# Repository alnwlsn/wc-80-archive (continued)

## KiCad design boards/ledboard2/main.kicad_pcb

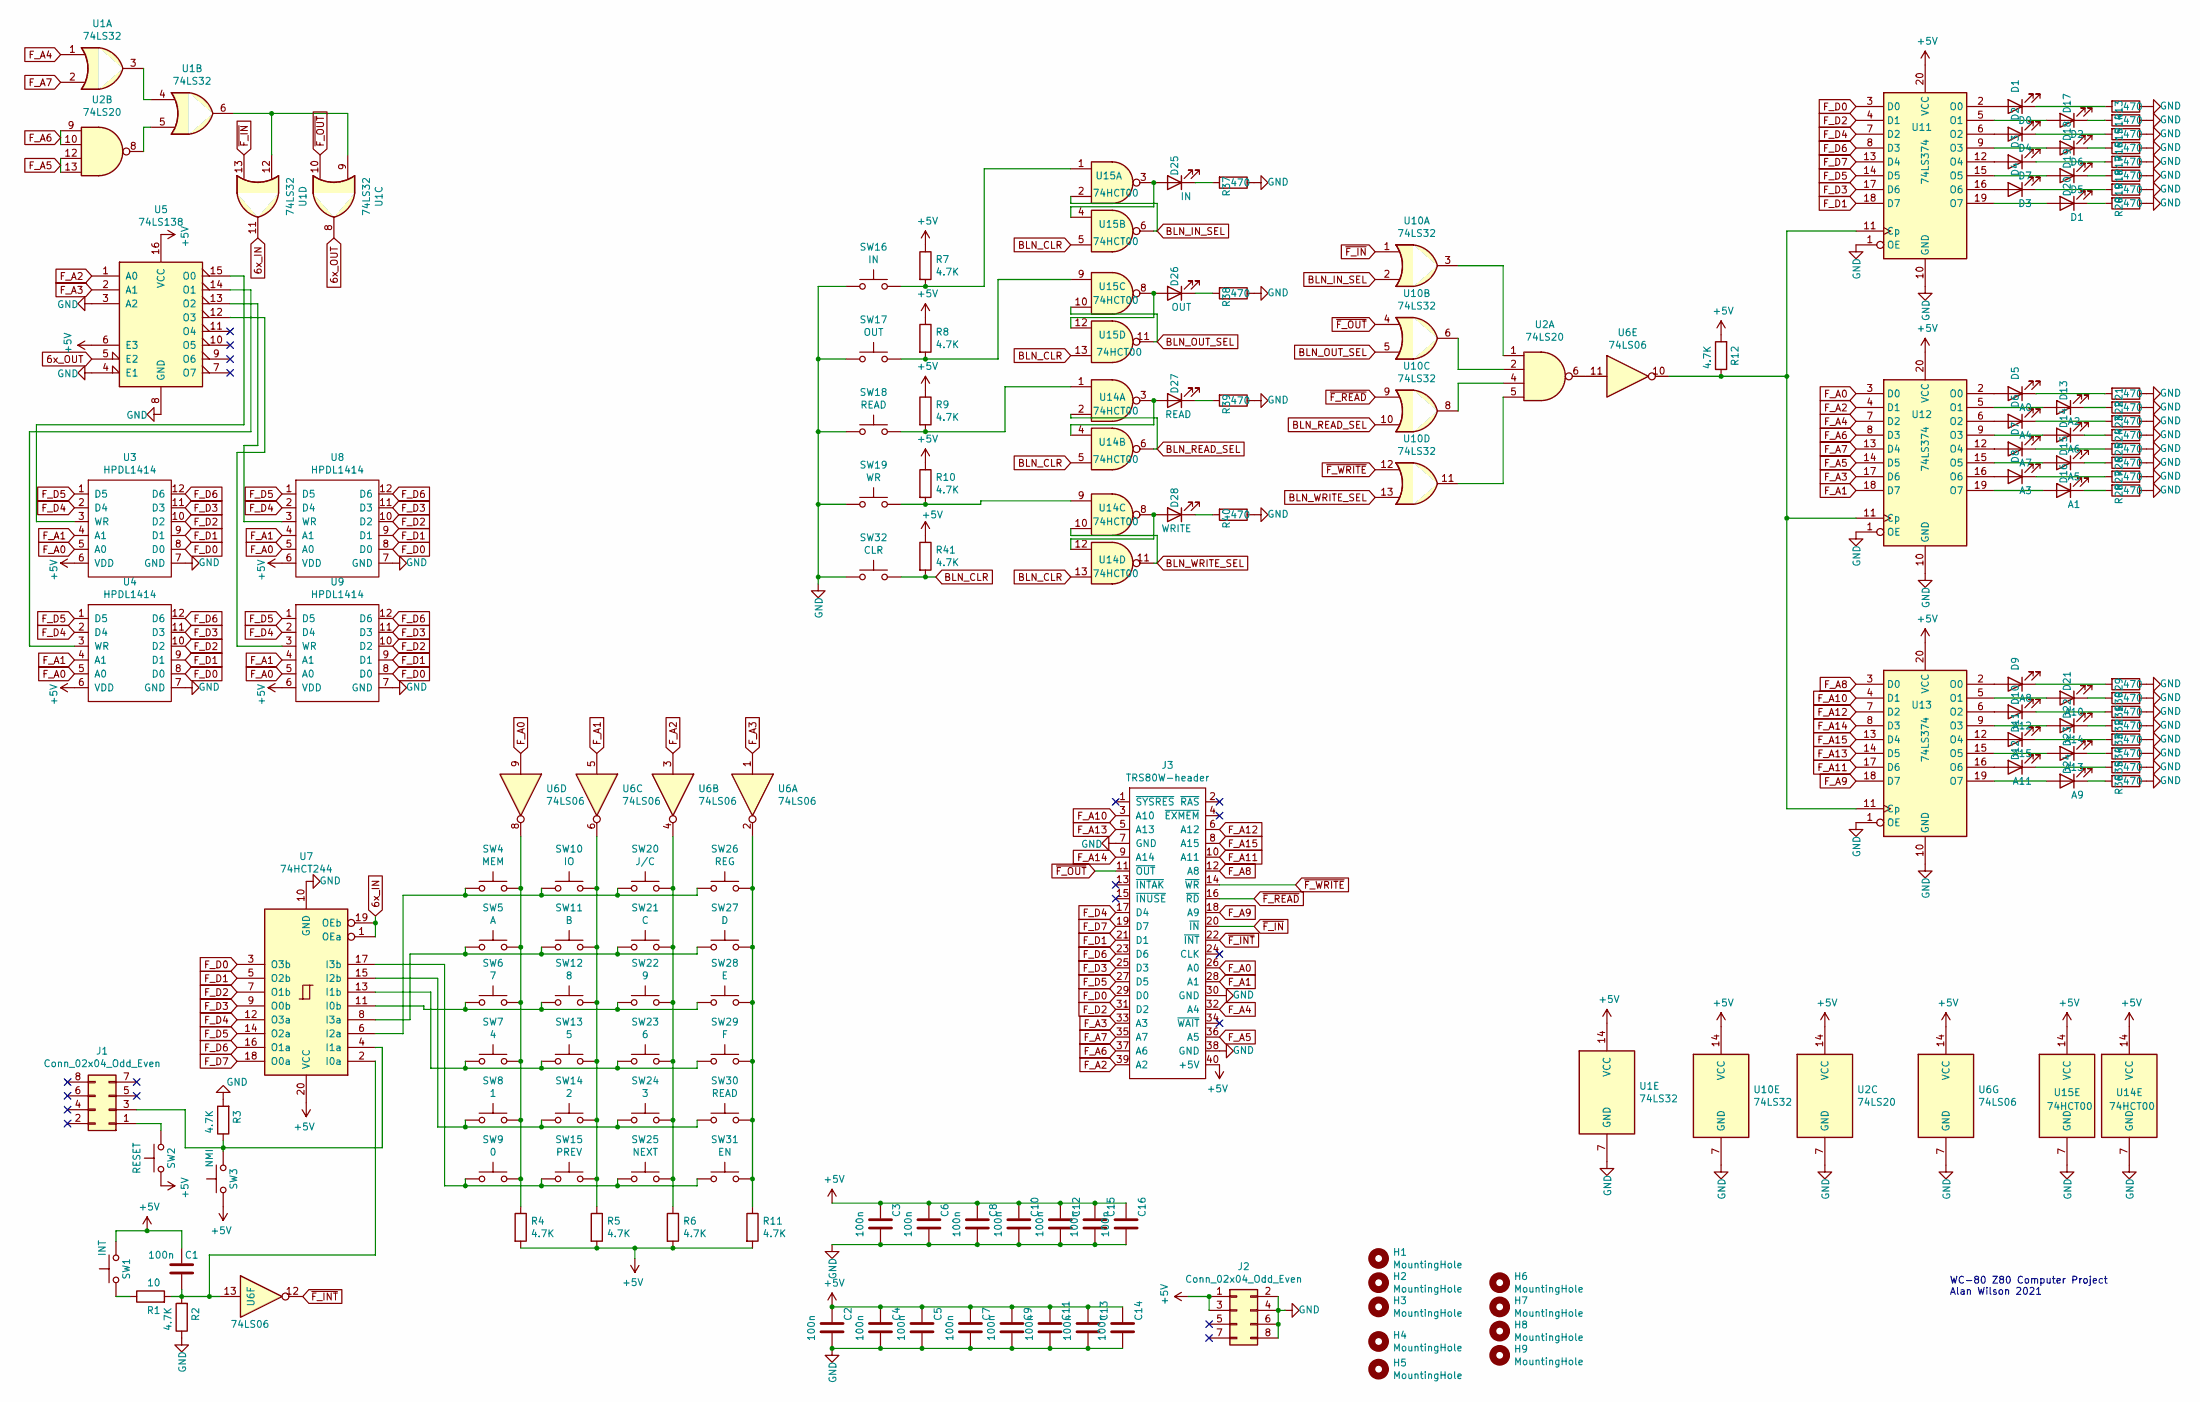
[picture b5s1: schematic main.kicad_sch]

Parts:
C1, C2, C3, C4, C5, C6, C7, C8, C9, C10, C11, C12, C13, C14, C15, C16: 100n; C_0805_2012Metric
D1: D0; LED_D3.0mm_FlatTop
D2: D4; LED_D3.0mm_FlatTop
D3: D7; LED_D3.0mm_FlatTop
D4: D3; LED_D3.0mm_FlatTop
D5: A0; LED_D3.0mm_FlatTop
D6: A4; LED_D3.0mm_FlatTop
D7: A7; LED_D3.0mm_FlatTop
D8: A3; LED_D3.0mm_FlatTop
D9: A8; LED_D3.0mm_FlatTop
D10: A12; LED_D3.0mm_FlatTop
D11: A15; LED_D3.0mm_FlatTop
D12: A11; LED_D3.0mm_FlatTop
D13: A2; LED_D3.0mm_FlatTop
D14: A6; LED_D3.0mm_FlatTop
D15: A5; LED_D3.0mm_FlatTop
D16: A1; LED_D3.0mm_FlatTop
D17: D2; LED_D3.0mm_FlatTop
D18: D6; LED_D3.0mm_FlatTop
D19: D5; LED_D3.0mm_FlatTop
D20: D1; LED_D3.0mm_FlatTop
D21: A10; LED_D3.0mm_FlatTop
D22: A14; LED_D3.0mm_FlatTop
D23: A13; LED_D3.0mm_FlatTop
D24: A9; LED_D3.0mm_FlatTop
D25: IN; LED_D3.0mm_FlatTop
D26: OUT; LED_D3.0mm_FlatTop
D27: READ; LED_D3.0mm_FlatTop
D28: WRITE; LED_D3.0mm_FlatTop
H1, H2, H3, H4, H5, H6, H7, H8, H9: MountingHole; MountingHole_3.2mm_M3_DIN965
J1, J2: Conn_02x04_Odd_Even; PinHeader_2x04_P2.54mm_Vertical
J3: TRS80W-header; PinHeader_2x20_P2.54mm_Vertical
R1: 10; R_0805_2012Metric
R2, R3, R4, R5, R6, R7, R8, R9, R10, R11, R12, R41: 4.7K; R_0805_2012Metric
R13, R14, R15, R16, R17, R18, R19, R20, R21, R22, R23, R24, R25, R26, R27, R28, R29, R30, R31, R32, R33, R34, R35, R36, R37, R38, R39, R40: 470; R_0805_2012Metric
SW1: INT; DTSL-6
SW2: RESET; DTSL-6
SW3: NMI; DTSL-6
SW4: MEM; DTSL-6
SW5: A; DTSL-6
SW6: 7; DTSL-6
SW7: 4; DTSL-6
SW8: 1; DTSL-6
SW9: 0; DTSL-6
SW10: IO; DTSL-6
SW11: B; DTSL-6
SW12: 8; DTSL-6
SW13: 5; DTSL-6
SW14: 2; DTSL-6
SW15: PREV; DTSL-6
SW16: IN; DTSL-6
SW17: OUT; DTSL-6
SW18, SW30: READ; DTSL-6
SW19: WR; DTSL-6
SW20: J/C; DTSL-6
SW21: C; DTSL-6
SW22: 9; DTSL-6
SW23: 6; DTSL-6
SW24: 3; DTSL-6
SW25: NEXT; DTSL-6
SW26: REG; DTSL-6
SW27: D; DTSL-6
SW28: E; DTSL-6
SW29: F; DTSL-6
SW31: EN; DTSL-6
SW32: CLR; DTSL-6
U1, U10: 74LS32; SOIC-14_3.9x8.7mm_P1.27mm
U2: 74LS20; SOIC-14_3.9x8.7mm_P1.27mm
U3, U4, U8, U9: HPDL1414; DIP-24_W15.24mm_Socket
U5: 74LS138; SOIC-16_3.9x9.9mm_P1.27mm
U6: 74LS06; SOIC-14_3.9x8.7mm_P1.27mm
U7: 74HCT244; SOIC-20W_7.5x12.8mm_P1.27mm
U11, U12, U13: 74LS374; SOIC-20W_7.5x12.8mm_P1.27mm
U14, U15: 74HCT00; SOIC-14_3.9x8.7mm_P1.27mm

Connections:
6x_IN: U1.11, U7.1 (OEa), U7.19 (OEb)
6x_OUT: U1.8, U5.5 (E2)
+5V: C1.2, C2.1, C3.1, C4.1, C5.1, C6.1, C7.1, C8.1, C9.1, C10.1, C11.1, C12.1, C13.1, C14.1, C15.1, C16.1, J2.1, J2.3, J3.40 (+5V), R4.2, R5.2, R6.2, R7.1, R8.1, R9.1, R10.1, R11.2, R12.2, R41.1, SW1.2, SW2.1, SW3.1, U1.14 (VCC), U2.14 (VCC), U3.6 (VDD), U4.6 (VDD), U5.6 (E3), U5.16 (VCC), U6.14 (VCC), U7.20 (VCC), U8.6 (VDD), U9.6 (VDD), U10.14 (VCC), U11.20 (VCC), U12.20 (VCC), U13.20 (VCC), U14.14 (VCC), U15.14 (VCC)
BLN_CLR: R41.2, SW32.2, U14.5, U14.13, U15.5, U15.13
BLN_IN_SEL: U10.2, U15.2, U15.6
BLN_OUT_SEL: U10.5, U15.10, U15.11
BLN_READ_SEL: U10.10, U14.2, U14.6
BLN_WRITE_SEL: U10.13, U14.10, U14.11
F_A0: J3.26 (A0), U3.5 (A0), U4.5 (A0), U6.9, U8.5 (A0), U9.5 (A0), U12.3 (D0)
F_A1: J3.28 (A1), U3.4 (A1), U4.4 (A1), U6.5, U8.4 (A1), U9.4 (A1), U12.18 (D7)
F_A2: J3.39 (A2), U5.1 (A0), U6.3, U12.4 (D1)
F_A3: J3.33 (A3), U5.2 (A1), U6.1, U12.17 (D6)
F_A4: J3.32 (A4), U1.1, U12.7 (D2)
F_A5: J3.36 (A5), U2.12, U2.13, U12.14 (D5)
F_A6: J3.37 (A6), U2.9, U2.10, U12.8 (D3)
F_A7: J3.35 (A7), U1.2, U12.13 (D4)
F_A8: J3.12 (A8), U13.3 (D0)
F_A9: J3.18 (A9), U13.18 (D7)
F_A10: J3.3 (A10), U13.4 (D1)
F_A11: J3.10 (A11), U13.17 (D6)
F_A12: J3.6 (A12), U13.7 (D2)
F_A13: J3.5 (A13), U13.14 (D5)
F_A14: J3.9 (A14), U13.8 (D3)
F_A15: J3.8 (A15), U13.13 (D4)
F_D0: J3.29 (D0), U3.8 (D0), U4.8 (D0), U7.3 (O3b), U8.8 (D0), U9.8 (D0), U11.3 (D0)
F_D1: J3.21 (D1), U3.9 (D1), U4.9 (D1), U7.5 (O2b), U8.9 (D1), U9.9 (D1), U11.18 (D7)
F_D2: J3.31 (D2), U3.10 (D2), U4.10 (D2), U7.7 (O1b), U8.10 (D2), U9.10 (D2), U11.4 (D1)
F_D3: J3.25 (D3), U3.11 (D3), U4.11 (D3), U7.9 (O0b), U8.11 (D3), U9.11 (D3), U11.17 (D6)
F_D4: J3.17 (D4), U3.2 (D4), U4.2 (D4), U7.12 (O3a), U8.2 (D4), U9.2 (D4), U11.7 (D2)
F_D5: J3.27 (D5), U3.1 (D5), U4.1 (D5), U7.14 (O2a), U8.1 (D5), U9.1 (D5), U11.14 (D5)
F_D6: J3.23 (D6), U3.12 (D6), U4.12 (D6), U7.16 (O1a), U8.12 (D6), U9.12 (D6), U11.8 (D3)
F_D7: J3.19 (D7), U7.18 (O0a), U11.13 (D4)
GND: C2.2, C3.2, C4.2, C5.2, C6.2, C7.2, C8.2, C9.2, C10.2, C11.2, C12.2, C13.2, C14.2, C15.2, C16.2, J2.2, J2.4, J2.6, J2.8, J3.7 (GND), J3.30 (GND), J3.38 (GND), R2.1, R3.2, R13.1, R14.1, R15.1, R16.1, R17.1, R18.1, R19.1, R20.1, R21.1, R22.1, R23.1, R24.1, R25.1, R26.1, R27.1, R28.1, R29.1, R30.1, R31.1, R32.1, R33.1, R34.1, R35.1, R36.1, R37.1, R38.1, R39.1, R40.1, SW16.1, SW17.1, SW18.1, SW19.1, SW32.1, U1.7 (GND), U2.7 (GND), U3.7 (GND), U4.7 (GND), U5.3 (A2), U5.4 (E1), U5.8 (GND), U6.7 (GND), U7.10 (GND), U8.7 (GND), U9.7 (GND), U10.7 (GND), U11.1 (OE), U11.10 (GND), U12.1 (OE), U12.10 (GND), U13.1 (OE), U13.10 (GND), U14.7 (GND), U15.7 (GND)
unnamed: D1.2 (A), U11.2 (O0)
unnamed: D1.1 (K), R13.2
unnamed: D2.2 (A), U11.6 (O2)
unnamed: D2.1 (K), R15.2
unnamed: D3.2 (A), U11.12 (O4)
unnamed: D3.1 (K), R17.2
unnamed: D4.2 (A), U11.16 (O6)
unnamed: D4.1 (K), R19.2
unnamed: D5.2 (A), U12.2 (O0)
unnamed: D5.1 (K), R21.2
unnamed: D6.2 (A), U12.6 (O2)
unnamed: D6.1 (K), R23.2
unnamed: D7.2 (A), U12.12 (O4)
unnamed: D7.1 (K), R25.2
unnamed: D8.2 (A), U12.16 (O6)
unnamed: D8.1 (K), R27.2
unnamed: D9.2 (A), U13.2 (O0)
unnamed: D9.1 (K), R29.2
unnamed: D10.2 (A), U13.6 (O2)
unnamed: D10.1 (K), R31.2
unnamed: D11.2 (A), U13.12 (O4)
unnamed: D11.1 (K), R33.2
unnamed: D12.2 (A), U13.16 (O6)
unnamed: D12.1 (K), R35.2
unnamed: D13.2 (A), U12.5 (O1)
unnamed: D13.1 (K), R22.2
unnamed: D14.2 (A), U12.9 (O3)
unnamed: D14.1 (K), R24.2
unnamed: D15.2 (A), U12.15 (O5)
unnamed: D15.1 (K), R26.2
unnamed: D16.2 (A), U12.19 (O7)
unnamed: D16.1 (K), R28.2
unnamed: D17.2 (A), U11.5 (O1)
unnamed: D17.1 (K), R14.2
unnamed: D18.2 (A), U11.9 (O3)
unnamed: D18.1 (K), R16.2
unnamed: D19.2 (A), U11.15 (O5)
unnamed: D19.1 (K), R18.2
unnamed: D20.2 (A), U11.19 (O7)
unnamed: D20.1 (K), R20.2
unnamed: D21.2 (A), U13.5 (O1)
unnamed: D21.1 (K), R30.2
unnamed: D22.2 (A), U13.9 (O3)
unnamed: D22.1 (K), R32.2
unnamed: D23.2 (A), U13.15 (O5)
unnamed: D23.1 (K), R34.2
unnamed: D24.2 (A), U13.19 (O7)
unnamed: D24.1 (K), R36.2
unnamed: D25.2 (A), U15.3, U15.4
unnamed: D25.1 (K), R37.2
unnamed: D26.2 (A), U15.8, U15.12
unnamed: D26.1 (K), R38.2
unnamed: D27.2 (A), U14.3, U14.4
unnamed: D27.1 (K), R39.2
unnamed: D28.2 (A), U14.8, U14.12
unnamed: D28.1 (K), R40.2
unnamed: J1.1, SW2.2
unnamed: J1.3, R3.1, SW3.2, U7.4 (I1a)
unnamed: R1.1, SW1.1
unnamed: R4.1, SW4.2, SW5.2, SW6.2, SW7.2, SW8.2, SW9.2, U6.8
unnamed: R5.1, SW10.2, SW11.2, SW12.2, SW13.2, SW14.2, SW15.2, U6.6
unnamed: R6.1, SW20.2, SW21.2, SW22.2, SW23.2, SW24.2, SW25.2, U6.4
unnamed: R7.2, SW16.2, U15.1
unnamed: R8.2, SW17.2, U15.9
unnamed: R9.2, SW18.2, U14.1
unnamed: R10.2, SW19.2, U14.9
unnamed: R11.1, SW26.2, SW27.2, SW28.2, SW29.2, SW30.2, SW31.2, U6.2
unnamed: U1.3, U1.4
unnamed: U1.5, U2.8
unnamed: U1.6, U1.9, U1.12
unnamed: U2.6, U6.11
unnamed: U3.3 (WR), U5.15 (O0)
unnamed: U4.3 (WR), U5.14 (O1)
unnamed: U5.13 (O2), U8.3 (WR)
unnamed: U5.12 (O3), U9.3 (WR)
unnamed: C1.1, R1.2, R2.2, U6.13, U7.2 (I0a)
unnamed: SW6.1, SW12.1, SW22.1, SW28.1, U7.11 (I0b)
unnamed: SW7.1, SW13.1, SW23.1, SW29.1, U7.13 (I1b)
unnamed: SW4.1, SW10.1, SW20.1, SW26.1, U7.6 (I2a)
unnamed: SW8.1, SW14.1, SW24.1, SW30.1, U7.15 (I2b)
unnamed: SW5.1, SW11.1, SW21.1, SW27.1, U7.8 (I3a)
unnamed: SW9.1, SW15.1, SW25.1, SW31.1, U7.17 (I3b)
unnamed: U2.1, U10.3
unnamed: U2.2, U10.6
unnamed: U2.4, U10.8
unnamed: U2.5, U10.11
unnamed: R12.1, U6.10, U11.11 (Cp), U12.11 (Cp), U13.11 (Cp)
~F_INT: J3.22 (~INT), U6.12
~F_IN: J3.20 (~IN), U1.13, U10.1
~F_OUT: J3.11 (~OUT), U1.10, U10.4
~F_READ: J3.16 (~RD), U10.9
~F_WRITE: J3.14 (~WR), U10.12

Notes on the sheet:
WC-80 Z80 Computer Project Alan Wilson 2021

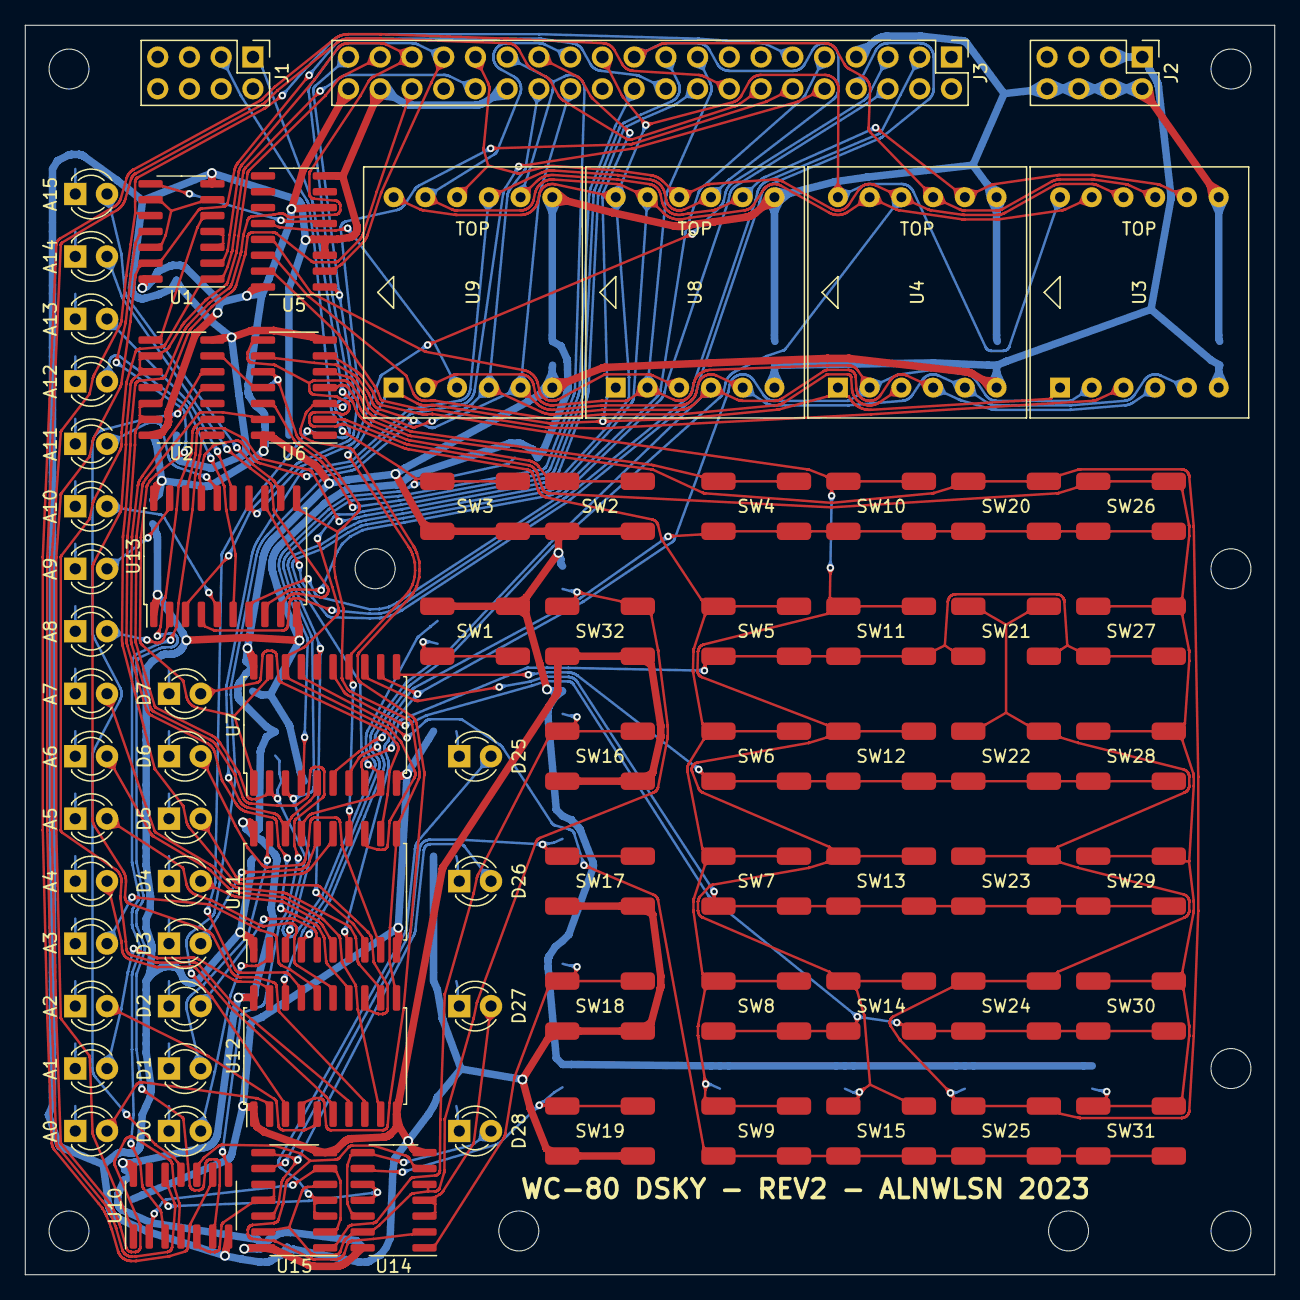
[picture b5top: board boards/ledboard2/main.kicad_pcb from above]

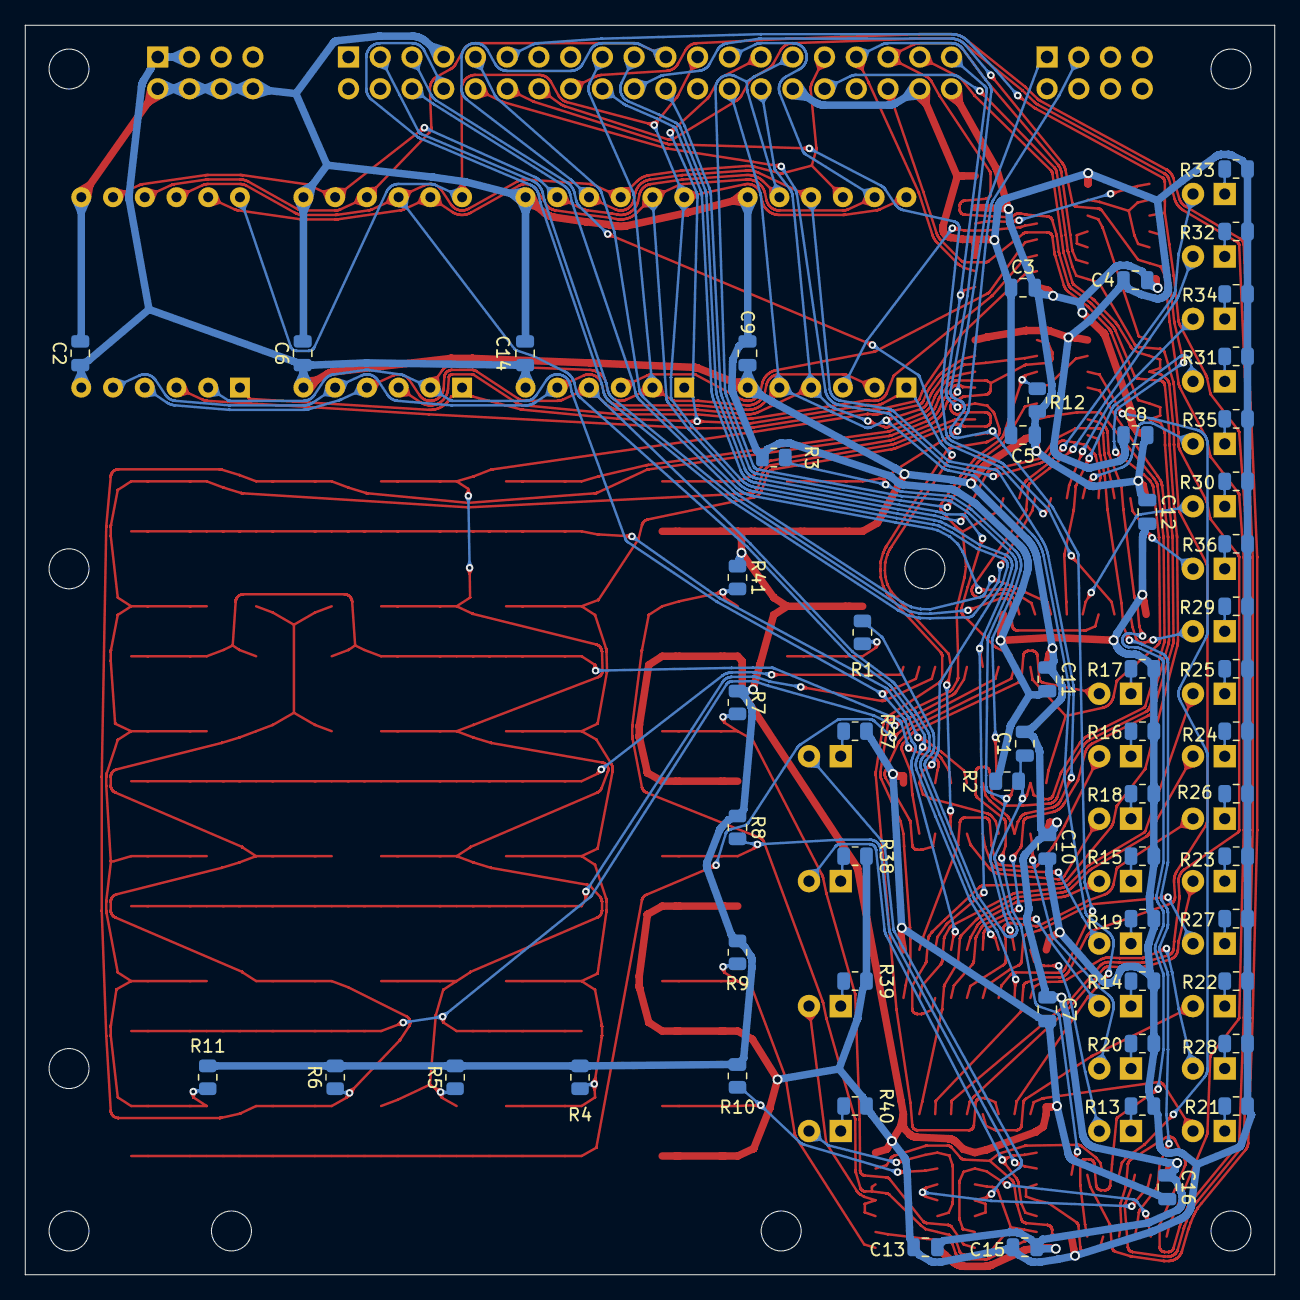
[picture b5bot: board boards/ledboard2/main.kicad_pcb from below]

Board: 2 copper layers, 100.0 x 100.0 mm, 144 parts (57 on the bottom side), 125 nets.

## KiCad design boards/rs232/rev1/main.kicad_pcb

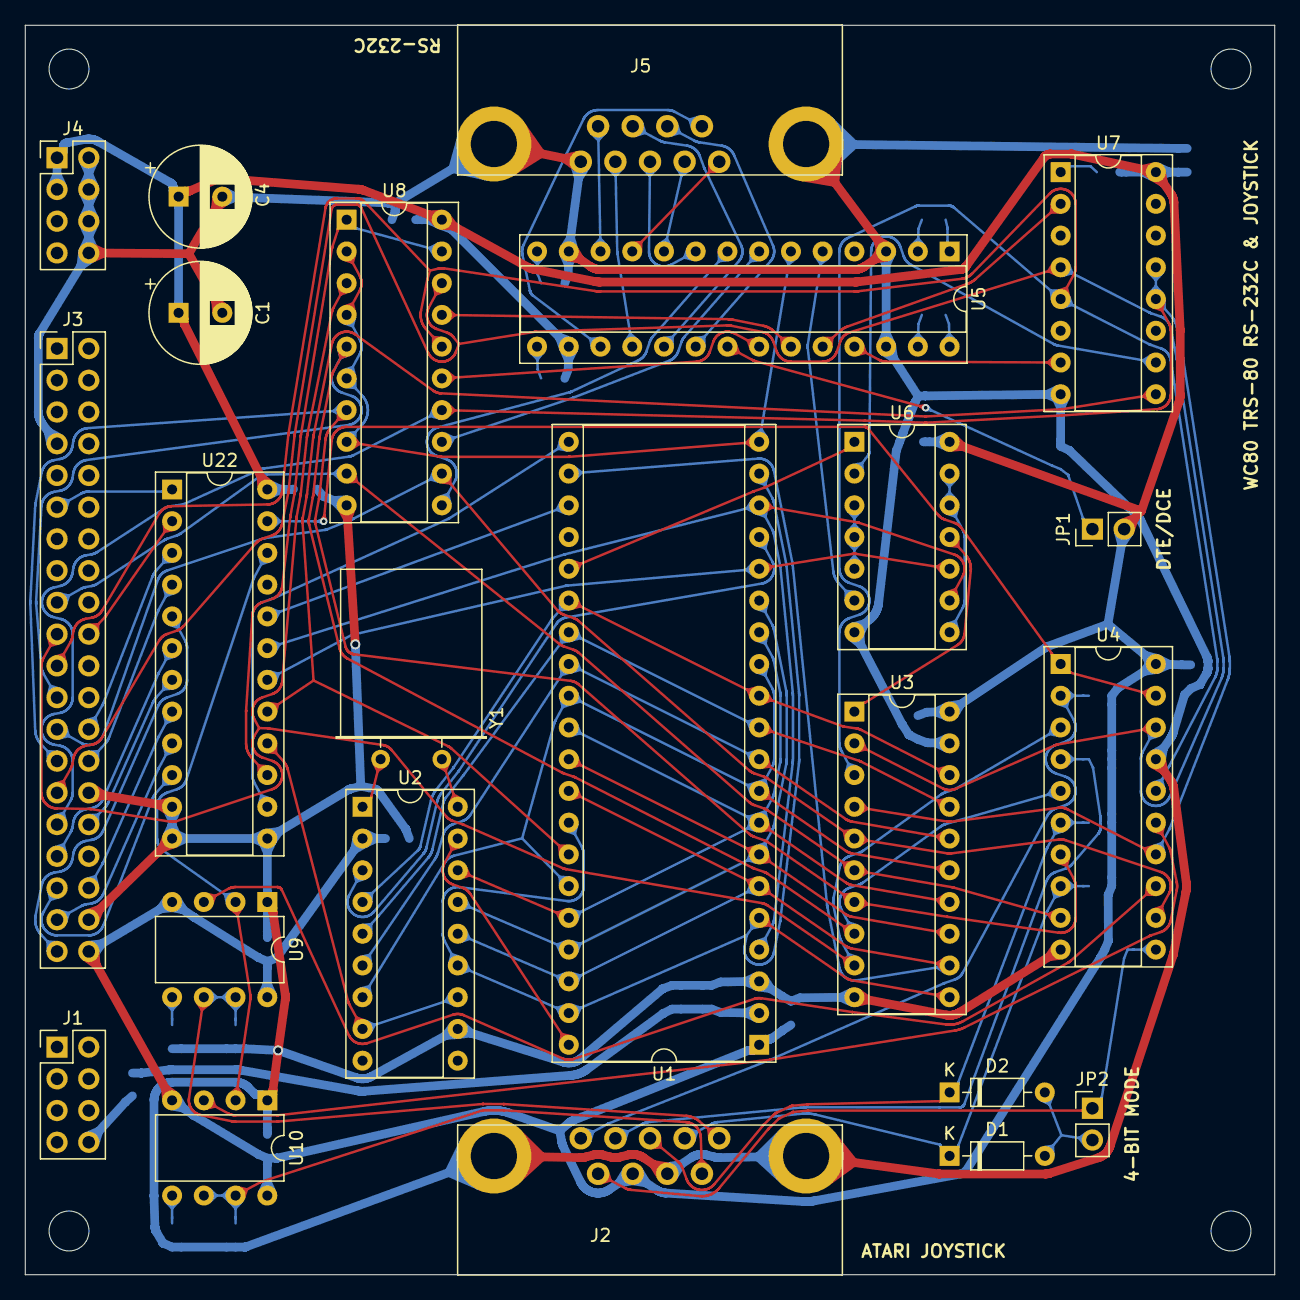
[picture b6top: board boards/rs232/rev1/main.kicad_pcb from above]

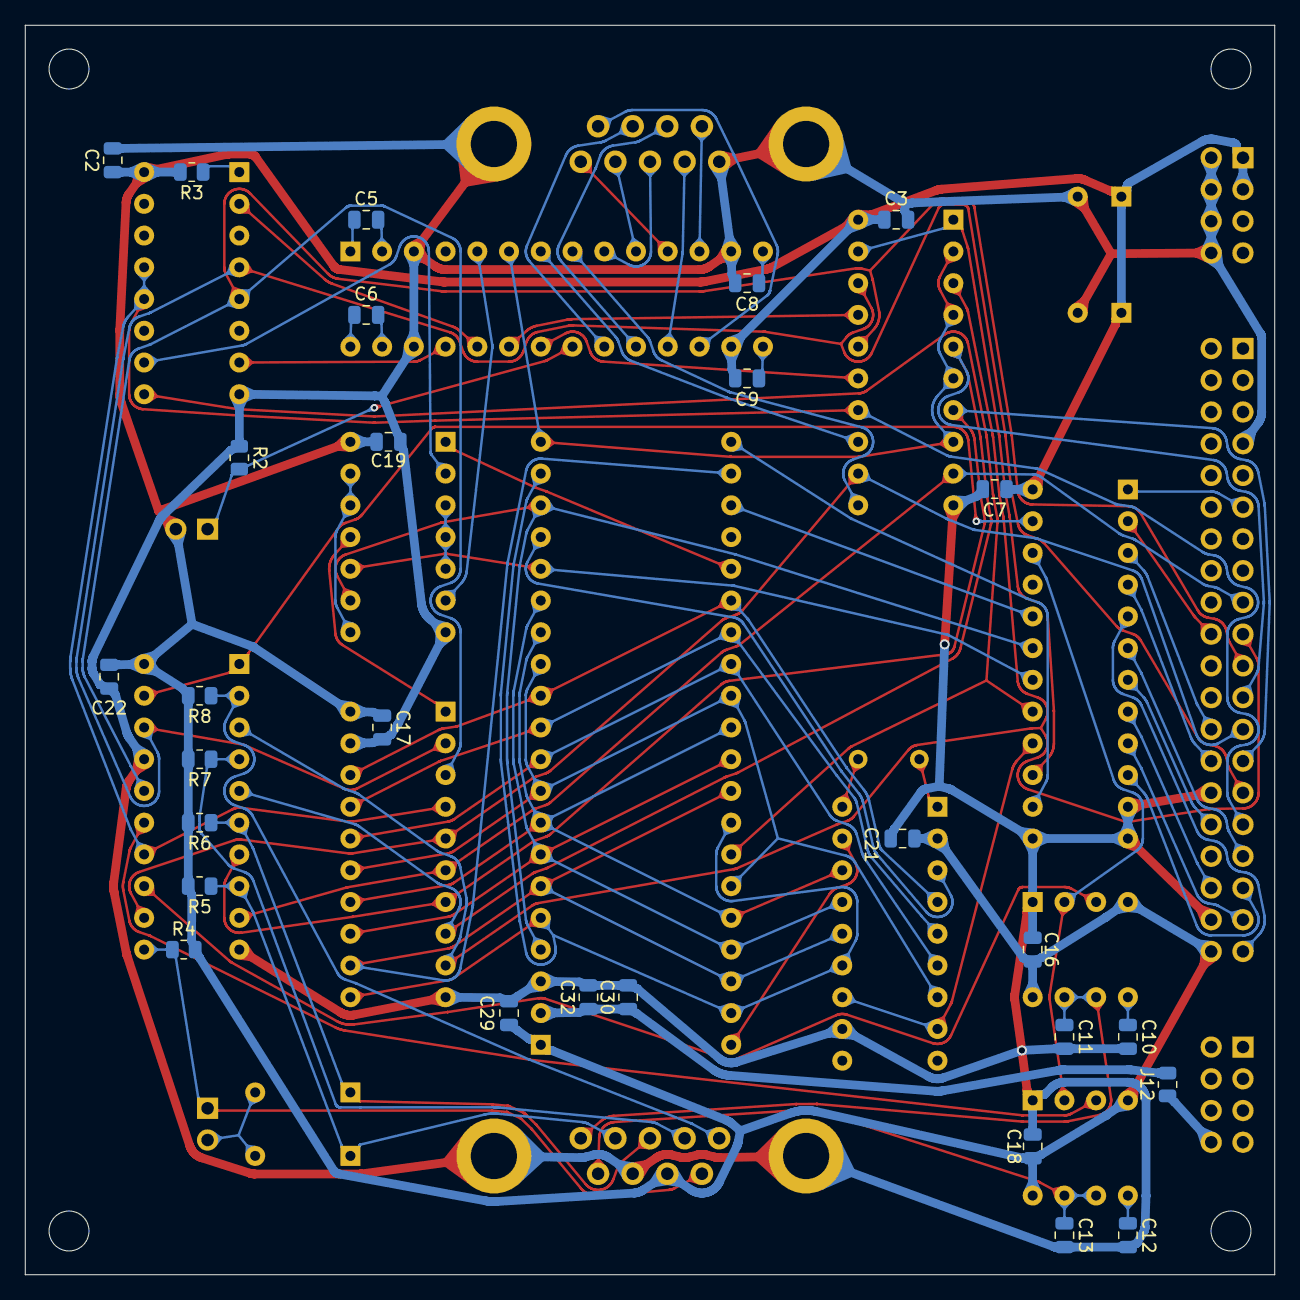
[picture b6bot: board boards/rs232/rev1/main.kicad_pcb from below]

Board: 2 copper layers, 100.0 x 100.0 mm, 55 parts (28 on the bottom side), 84 nets.

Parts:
C1, C4: 470uF; CP_Radial_D8.0mm_P3.50mm
C2, C3, C16, C17, C18, C19, C21, C22, C29, C32: 100n; C_0805_2012Metric
C5, C6, C7, C8, C9: 1u; C_0805_2012Metric
C10, C11, C12, C13: 10n; C_0805_2012Metric
C30: 10uF; C_0805_2012Metric
D1, D2: 1N4148; D_DO-35_SOD27_P7.62mm_Horizontal
J1, J4: Conn_02x04_Odd_Even; PinHeader_2x04_P2.54mm_Vertical
J2: JOYSTICK; DS1037-09MNAKT74-0CC
J3: TRS80W-header; PinHeader_2x20_P2.54mm_Vertical
J5: RS-232C; DS1037-09MNAKT74-0CC
J12: 0 (optional); R_0805_2012Metric
JP1: DCE; PinHeader_1x02_P2.54mm_Vertical
JP2: 4BIT; PinHeader_1x02_P2.54mm_Vertical
M1, M2, M3, M4: 3mm-mounting-hole; MountingHole_3.2mm_M3_DIN965
R2, R3, R4, R5, R6, R7, R8: 10K; R_0805_2012Metric
U1: TR1602-UART; DIP-40_W15.24mm_Socket
U2: COM8136; DIP-18_W7.62mm_Socket
U3: 74LS245; DIP-20_W7.62mm_Socket
U4, U8: 74LS244; DIP-20_W7.62mm_Socket
U5: MAX214; DIP-28_W7.62mm_Socket
U6: 74LS00; DIP-14_W7.62mm_Socket
U7: 74LS175; DIP-16_W7.62mm_Socket
U9, U10: LM555xN; DIP-8_W7.62mm
U22: ATF22V10C; DIP-24_W7.62mm_Socket
Y1: 5.0688 mHz; Crystal_HC49-U_Horizontal

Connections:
+5V: C1.1, C2.1, C3.1, C4.1, C7.1, C9.2, C16.1, C17.1, C18.1, C19.1, C21.1, C22.1, C29.1, J2.7, J3.40, J4.1, J4.3, JP1.2, R3.2, R4.2, R5.2, R6.2, R7.2, R8.2, U1.1, U2.2, U3.20, U4.20, U5.16, U6.14, U7.16, U8.20, U9.4, U9.8, U10.4, U10.8, U22.24
-12V: C30.1, C32.1, J12.2, U1.2
BRG: U2.8, U2.12, U22.16
CTS: U5.23, U8.17
CTS-H: J5.8, U5.19
D0: U1.12, U1.26, U2.4, U3.18
D1: U1.11, U1.27, U2.5, U3.17
D2: U1.10, U1.28, U2.6, U3.16
D3: U1.9, U1.13, U1.29, U1.35, U2.7, U3.15
D4: U1.8, U1.14, U1.30, U1.36, U2.16, U3.14
D5: U1.7, U1.15, U1.31, U1.37, U2.15, U3.13
D6: U1.6, U1.22, U1.32, U1.38, U2.14, U3.12
D7: U1.5, U1.19, U1.33, U1.39, U2.13, U3.11
DCD: U5.7, U8.13
DCD-H: J5.1, U5.11
DSR: U5.22, U8.15
DSR-H: J5.6, U5.17
DTR: U5.24, U7.2
DTR-H: J5.4, U5.18
E8-out: U1.21, U22.14
EA-out: U1.34, U7.9, U22.17
FR: U1.17, U2.3
FT: U1.40, U2.17
F_A0: J3.26, U22.3
F_A1: J3.28, U22.4
F_A2: J3.39, U22.5
F_A3: J3.33, U22.6
F_A4: J3.32, U22.7
F_A5: J3.36, U22.8
F_A6: J3.37, U22.9
F_A7: J3.35, U22.10
F_D0: J3.29, U3.2, U4.18, U7.4, U8.18
F_D1: J3.21, U3.3, U4.16, U7.5, U8.16
F_D2: J3.31, U3.4, U4.14, U7.12, U7.13, U8.14
F_D3: J3.25, U3.5, U4.12, U8.12
F_D4: J3.17, U3.6, U4.9, U8.9
F_D5: J3.27, U3.7, U4.7, U8.7
F_D6: J3.23, U3.8, U4.5, U8.5
F_D7: J3.19, U3.9, U4.3, U8.3
GND: C1.2, C2.2, C3.2, C4.2, C7.2, C8.2, C10.2, C11.2, C12.2, C13.2, C16.2, C17.2, C18.2, C19.2, C21.2, C22.2, C29.2, C30.2, C32.2, J2.0, J2.8, J3.7, J3.30, J3.38, J4.2, J4.4, J4.6, J4.8, J5.0, J5.5, R2.1, U1.3, U2.11, U3.10, U3.19, U4.10, U4.17, U5.3, U5.13, U5.26, U6.7, U7.8, U8.10, U9.1, U10.1, U22.11, U22.12, U22.13
JSTK: U4.1, U4.19, U22.23
unnamed: C5.1, U5.1
unnamed: C5.2, U5.2
unnamed: C6.1, U5.28
unnamed: C6.2, U5.27
unnamed: C8.1, U5.14
unnamed: C9.1, U5.15
unnamed: C10.1, U9.5
unnamed: C11.1, J2.5, U9.6, U9.7
unnamed: C12.1, U10.5
unnamed: C13.1, J2.9, U10.6, U10.7
unnamed: D1.1, J2.4, R5.1, U4.8
unnamed: D1.2, D2.2, JP2.2
unnamed: D2.1, J2.3, R6.1, U4.6
unnamed: J1.8, J12.1
unnamed: J2.1, R8.1, U4.2
unnamed: J2.2, R7.1, U4.4
unnamed: J2.6, JP2.1, R4.1, U4.11
unnamed: JP1.1, R2.2, U5.21
unnamed: R3.1, U7.1
unnamed: U1.25, U6.1
unnamed: U2.1, Y1.2
unnamed: U2.18, Y1.1
unnamed: U3.1, U6.11
unnamed: U4.13, U9.3
unnamed: U6.2, U7.10
unnamed: U6.3, U6.4, U6.5
unnamed: U6.8, U6.12, U6.13
unnamed: U4.15, U10.3
RI: U5.8, U8.11
RI-H: J5.9, U5.12
RTS: U5.25, U7.7
RTS-H: J5.7, U5.20
RXD: U1.20, U5.6, U8.2, U8.4, U8.6, U8.8
RXD-H: J5.2, U5.10
TXD: U5.5, U6.6
TXD-H: J5.3, U5.9
~E8-in~: U8.1, U8.19, U22.15
~EA-in~: U1.16, U6.10, U22.18
~EB-in~: U1.4, U1.18, U6.9, U22.19
~EB-out~: U1.23, U22.20
~F_IN~: J3.20, U22.2
~F_OUT~: J3.11, U22.1
~PADTRG~: U9.2, U10.2, U22.22
